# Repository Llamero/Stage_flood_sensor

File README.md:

# Stage Flood Sensor

## Summary:

This is an open-source liquid sensor for microscopes.  It works by measuring the resistance between pairs of conductors separated by 550 µm.

The four-layer layout with a grid of vias connecting to the layers allows for the the sensor board to be cut and shaped as needed without interfering with the electrical connections.  

## Installation (Arduino Uno):

1) Order the sensor PCB by uploading the provided Gerber files to a PCB manufacturer such as [OSH Park](https://oshpark.com/), [PCBWay](https://www.pcbway.com/orderonline.aspx), [Ailser](https://aisler.net/), etc.
2) If using an Arduino, order the following items:
- [Arduino Uno](https://www.digikey.com/en/products/detail/arduino/A000066/2784006)
- [Piezo transducer](https://www.digikey.com/en/products/detail/mallory-sonalert-products-inc/PT-2038WQ/1957869)
- [10 kOhm throughhole resistor](https://www.digikey.com/en/products/detail/stackpole-electronics-inc/CF14JT10K0/1741265)
- [Header pins](https://www.digikey.com/en/products/detail/w%C3%BCrth-elektronik/61300811121/4846839)
- Wires and solder
- Note: If using the [High-Speed Programmable LED Driver](https://github.com/Llamero/Four_Channel_MHz_LED_Driver), the sensor can connect directly to the external thermistor port, so only wire and solder is needed.
3) Cut/drill the sensor PCB as needed
4) Solder across both jumpers if an RC filter isn't used, otherwise solder on the desired resistor and capacitor combination.

5) Solder a pair of wires to the two wire pads.

6) Cut a set of 5 pins from the header pins.
7) Solder the 10 kOhm resistor between the 5V pin and A0 pin on the arduino.
8) Solder the positive wire to pin A0.
9) Solder the negative wire to GND.

10) Cut a pair of pins from the header pins.
11) Solder the two piezo wires to the pins (polarity does not matter).
12) Insert the pins to digital pins 6 and 7.
13) Upload the provided code to the Arduino.

## Installation (LED Driver):

1) Follow steps 1-5 for the Arduino Uno installation
2) Connect the wires to the "External Therm" port on the LED driver.
3) Set the "External Fault" temperature to 0° and the "External Warn" temperature to 1°C.  For higher sensitivity, also increase the "Resistance at 25°C" value.  For example, a value of 90000 will allow the sensor to detect deionized water.

## Troubleshooting 

Test the driver by applying a drop of water or PBS onto the sensor.  This should trip the alarm and wiping the liquid off should reset the alarm:
- [Arduino alarm example](https://www.youtube.com/watch?v=3DOJQmaSFc4&ab_channel=BenjaminESmith)
- [LED driver example](https://www.youtube.com/watch?v=jpRJdUz0464&ab_channel=BenjaminESmith)

If the alarm trips without liquid, this means there is a short on the board.  If the board was cut or drilled, then sand these regions and inspect the board under a microscope for any shorting traces.

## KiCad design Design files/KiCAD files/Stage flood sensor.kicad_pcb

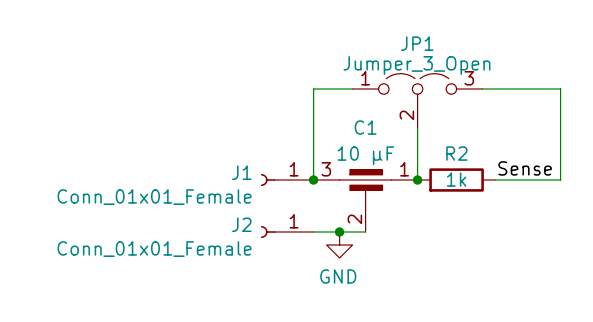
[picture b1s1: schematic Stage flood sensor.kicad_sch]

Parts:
C1: 10 µF; 0603 Passthrough capacitor; Part # YFF18PH0J106MT00HE
J1, J2: Conn_01x01_Female; SolderWirePad_1x01_SMD_5x10mm
JP1: Jumper_3_Open; SolderJumper-3_P2.0mm_Open_TrianglePad1.0x1.5mm_NumberLabels
R2: 1k; R_0603_1608Metric; Part # RNCP0603FTD1K00

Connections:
/Sense: JP1.3 (B), R2.1
GND: C1.2, J2.1
unnamed: C1.3, J1.1, JP1.1 (A)
unnamed: C1.1, JP1.2 (C), R2.2

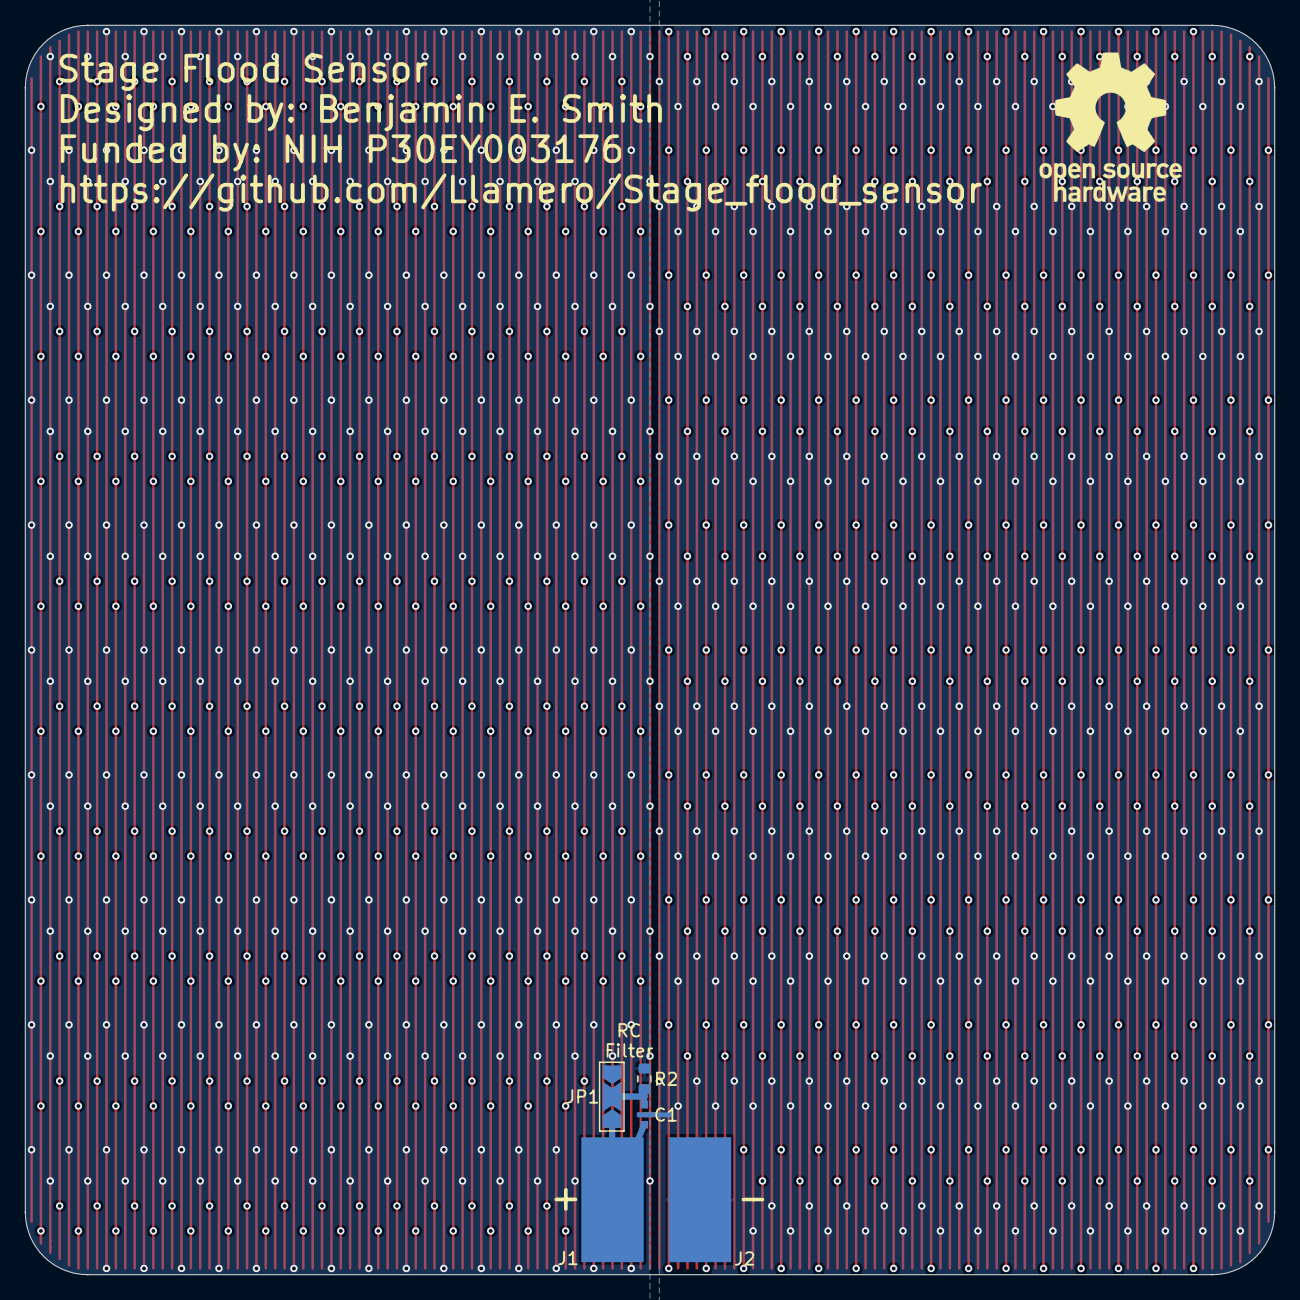
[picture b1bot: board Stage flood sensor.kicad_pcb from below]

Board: 4 copper layers, 100.0 x 100.0 mm, 5 parts (5 on the bottom side), 4 nets.

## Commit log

2023-04-20 Ordered
2023-05-06 Add Arduino code
2023-05-06 Add option for different boot volume
2023-05-06 Organize directories
2023-06-23 better comments
2023-06-30 Add images for README
2023-06-30 Add GUI
2023-06-30 Rename README to README.md
